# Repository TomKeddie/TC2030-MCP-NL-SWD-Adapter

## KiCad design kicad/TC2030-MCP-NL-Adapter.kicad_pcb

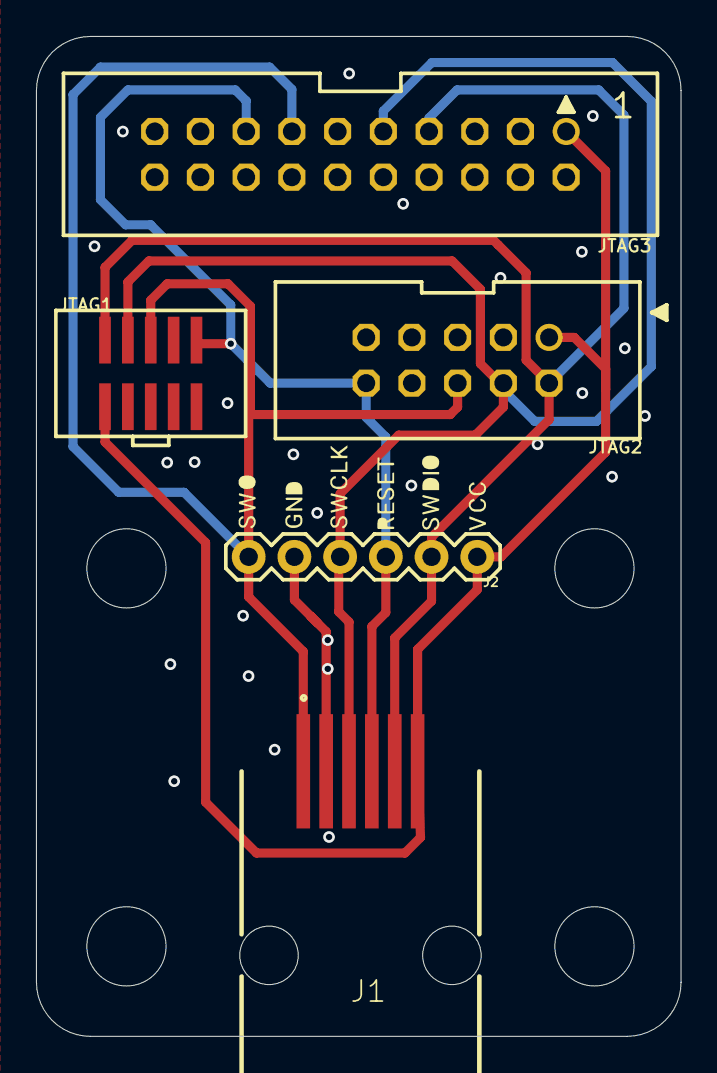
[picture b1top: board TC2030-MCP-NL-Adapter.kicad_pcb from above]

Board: 2 copper layers, 35.8 x 55.6 mm, 15 parts (0 on the bottom side), 6 nets.

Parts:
@HOLE0, @HOLE1, @HOLE2, @HOLE3: (no value)
J1: 95501-6669
J2: 1X06
JTAG1: 2X05_1.27MM_SMT
JTAG2: CORTEXM3_SWD10_MOLEX
JTAG3: JTAG-ARM
U$1: SWO0
U$2: GND0
U$3: SWCLK0
U$4: RESET0
U$5: SWDIO0
U$6: VCC0

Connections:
GND: J1.2, J2.5, JTAG1.3, JTAG1.5, JTAG1.9, JTAG2.3, JTAG2.5, JTAG2.9, JTAG3.4, JTAG3.6, JTAG3.8
RESET: J1.4, J2.3, JTAG1.10, JTAG2.10, JTAG3.15
SWCLK: J1.3, J2.4, JTAG1.4, JTAG2.4, JTAG3.9
SWDIO: J1.5, J2.2, JTAG1.2, JTAG2.2, JTAG3.7
SWO: J1.1, J2.6, JTAG1.6, JTAG2.6, JTAG3.13
VCC: J1.6, J2.1, JTAG1.1, JTAG2.1, JTAG3.1

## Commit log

2022-05-12 import eagle files into kicad
